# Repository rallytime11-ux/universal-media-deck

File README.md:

# universal-media-deck
What I am trying to do? It's a wireless, Bluetooth controller for listening to music/general media playing in desktop. It allows me to control volume and skip tracks without pressing alt-tab or closing tab when I am doing another task. Unlike standard macro pads/controller, this can rotary encoder for volume and an integrated LCD screen.

My planning: I will use an ESP32-C3 or S3 microcontroller. It will broadcast itself as a Bluetooth HID.
It can volume up and down with the knob. Media next/prev/pause using the buttons. A small screen provide visual feedback.

| Part | Est. Cost ($AUD) | Purpose |
| :--- | :--- | :--- |
| **Seeeduino XIAO ESP32S3** | ~$11 | Microcontroller with **Bluetooth HID** and Wi-Fi capabilities to drive the screen and handle inputs. |
| **1.28" Round LCD (GC9A01)** | ~$7 | High-resolution circular display for visual feedback (volume levels, layer status, animations). |
| **Rotary Encoder (EC11)** | ~$3 | **Through-hole** infinite rotation knob for volume control; includes an integrated push-button (Mute/Play). |
| **Mechanical Switches (x3)** | ~$2 | **Through-hole** tactile switches for media controls (Previous, Play/Pause, Next). |
| **LiPo Battery (500-1000mAh)** | ~$7 | Rechargeable power source to make the device completely wireless. |
| **SPDT Slide Switch** | ~$1 | Physical toggle switch to cut power from the battery when not in use. |
| **3D Printed Case** | Print it at school | Enclosure to house the electronics, hold the screen at a 45° angle (Required for T4/T5).|
| **Custom PCB** | ~$4 | Connects all components without messy wiring. *I have a $10 voucher.* |
| **Total Parts Cost (Cash)** | **~$35**(excluding shipping fee)/~$52(including shipping) | **This fits into the Tier 4 budget ($37 usd).** |

Planning Graph
Schmedic: 

PCB
2D:

3D
Front:

Back:

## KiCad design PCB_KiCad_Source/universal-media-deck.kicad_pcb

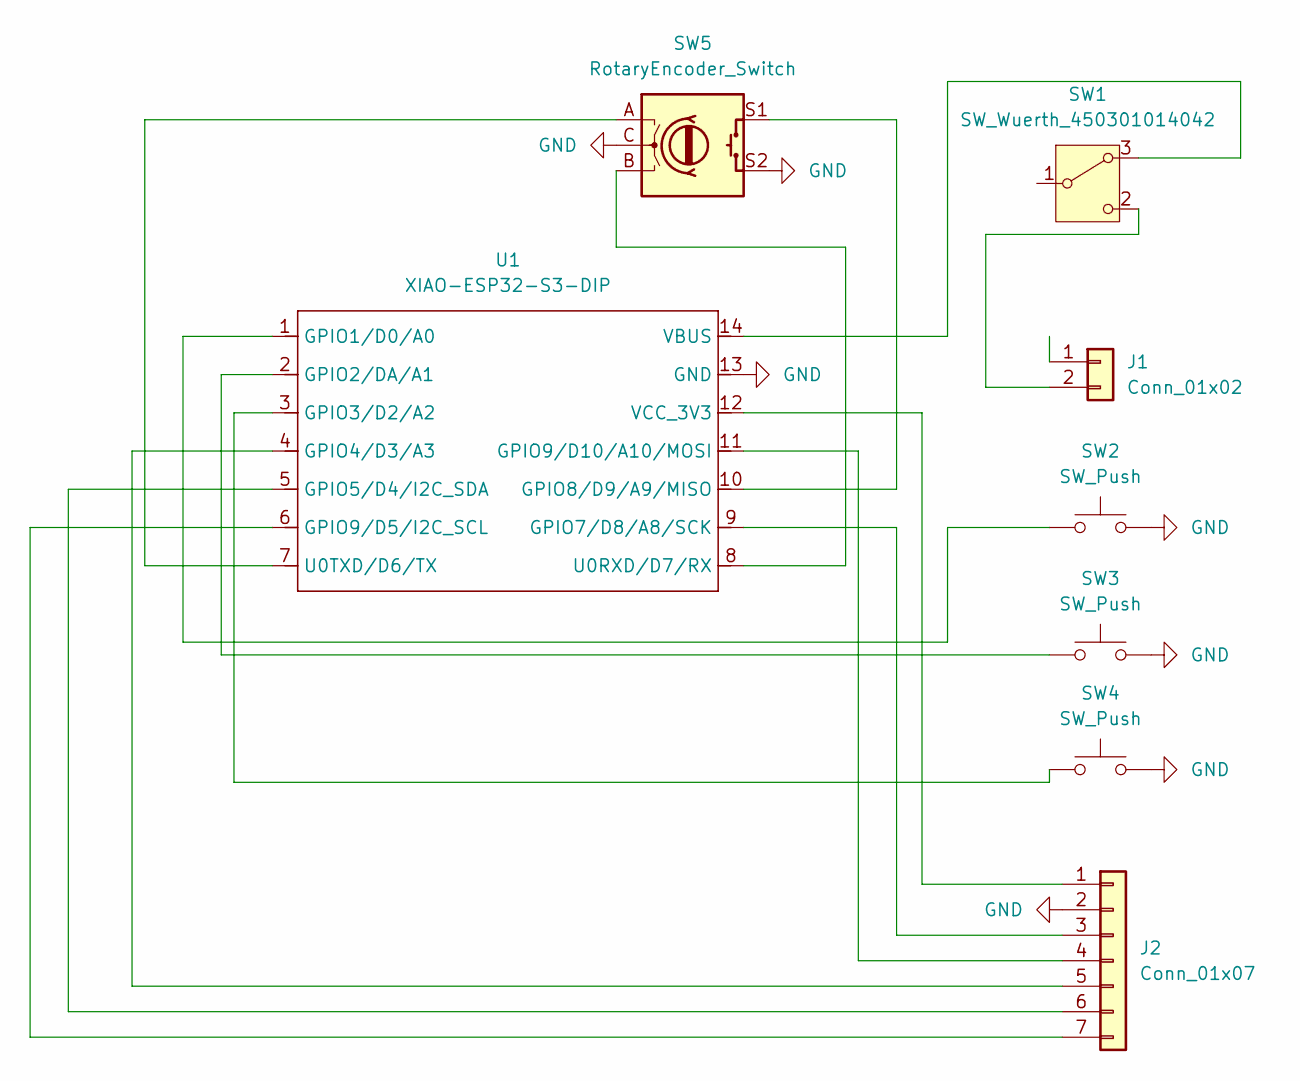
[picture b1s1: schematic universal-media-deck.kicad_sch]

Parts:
J1: Conn_01x02; JST_PH_S2B-PH-K_1x02_P2.00mm_Horizontal
J2: Conn_01x07; PinHeader_1x07_P2.54mm_Vertical
SW1: SW_Wuerth_450301014042; PinHeader_1x03_P2.54mm_Vertical
SW2, SW3, SW4: SW_Push; SW_Cherry_MX_1.00u_PCB
SW5: RotaryEncoder_Switch; RotaryEncoder_Alps_EC11E-Switch_Vertical_H20mm
U1: XIAO-ESP32-S3-DIP; XIAO-ESP32C3-DIP

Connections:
GND: J2.2, SW2.2, SW3.2, SW4.2, SW5.C, SW5.S2, U1.13 (GND)
unnamed: J1.2, SW1.2 (C)
unnamed: J2.1, U1.12 (VCC_3V3)
unnamed: J2.3, U1.9 (GPIO7/D8/A8/SCK)
unnamed: J2.4, U1.11 (GPIO9/D10/A10/MOSI)
unnamed: J2.5, U1.4 (GPIO4/D3/A3)
unnamed: J2.6, U1.5 (GPIO5/D4/I2C_SDA)
unnamed: J2.7, U1.6 (GPIO9/D5/I2C_SCL)
unnamed: SW1.3 (A), U1.14 (VBUS)
unnamed: SW2.1, U1.1 (GPIO1/D0/A0)
unnamed: SW3.1, U1.2 (GPIO2/DA/A1)
unnamed: SW4.1, U1.3 (GPIO3/D2/A2)
unnamed: SW5.S1, U1.10 (GPIO8/D9/A9/MISO)
unnamed: SW5.B, U1.8 (U0RXD/D7/RX)
unnamed: SW5.A, U1.7 (U0TXD/D6/TX)

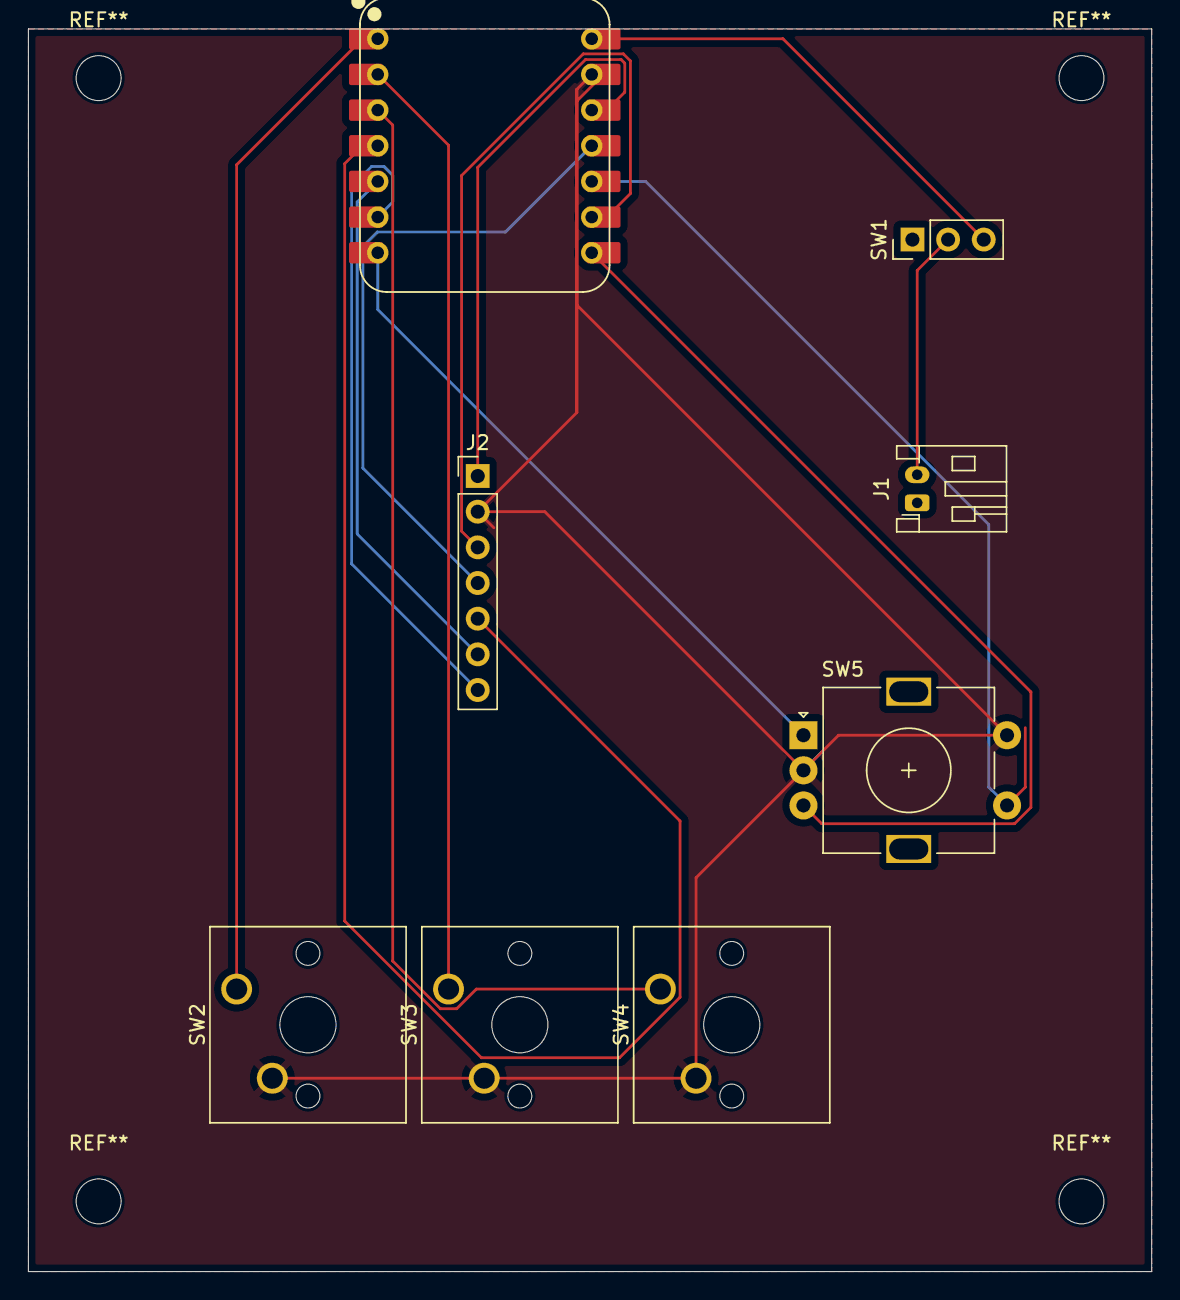
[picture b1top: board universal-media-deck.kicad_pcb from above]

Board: 2 copper layers, 80.0 x 88.5 mm, 8 parts (0 on the bottom side), 15 nets.

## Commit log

2025-12-13 Update README.md
    this is the second version of my project which make the media deck more reliable and better.
2025-12-13 PCB_KiCad_Source
2025-12-13 Manufacturing_Files
2025-12-13 Create C++ code
2025-12-14 uploaded new version of PCB_KiCad_Source
2025-12-14 update version of Manufacturing_Files
2026-03-09 Universal_Media_Deck_Case.stl
2026-03-09 Update README.md price table
